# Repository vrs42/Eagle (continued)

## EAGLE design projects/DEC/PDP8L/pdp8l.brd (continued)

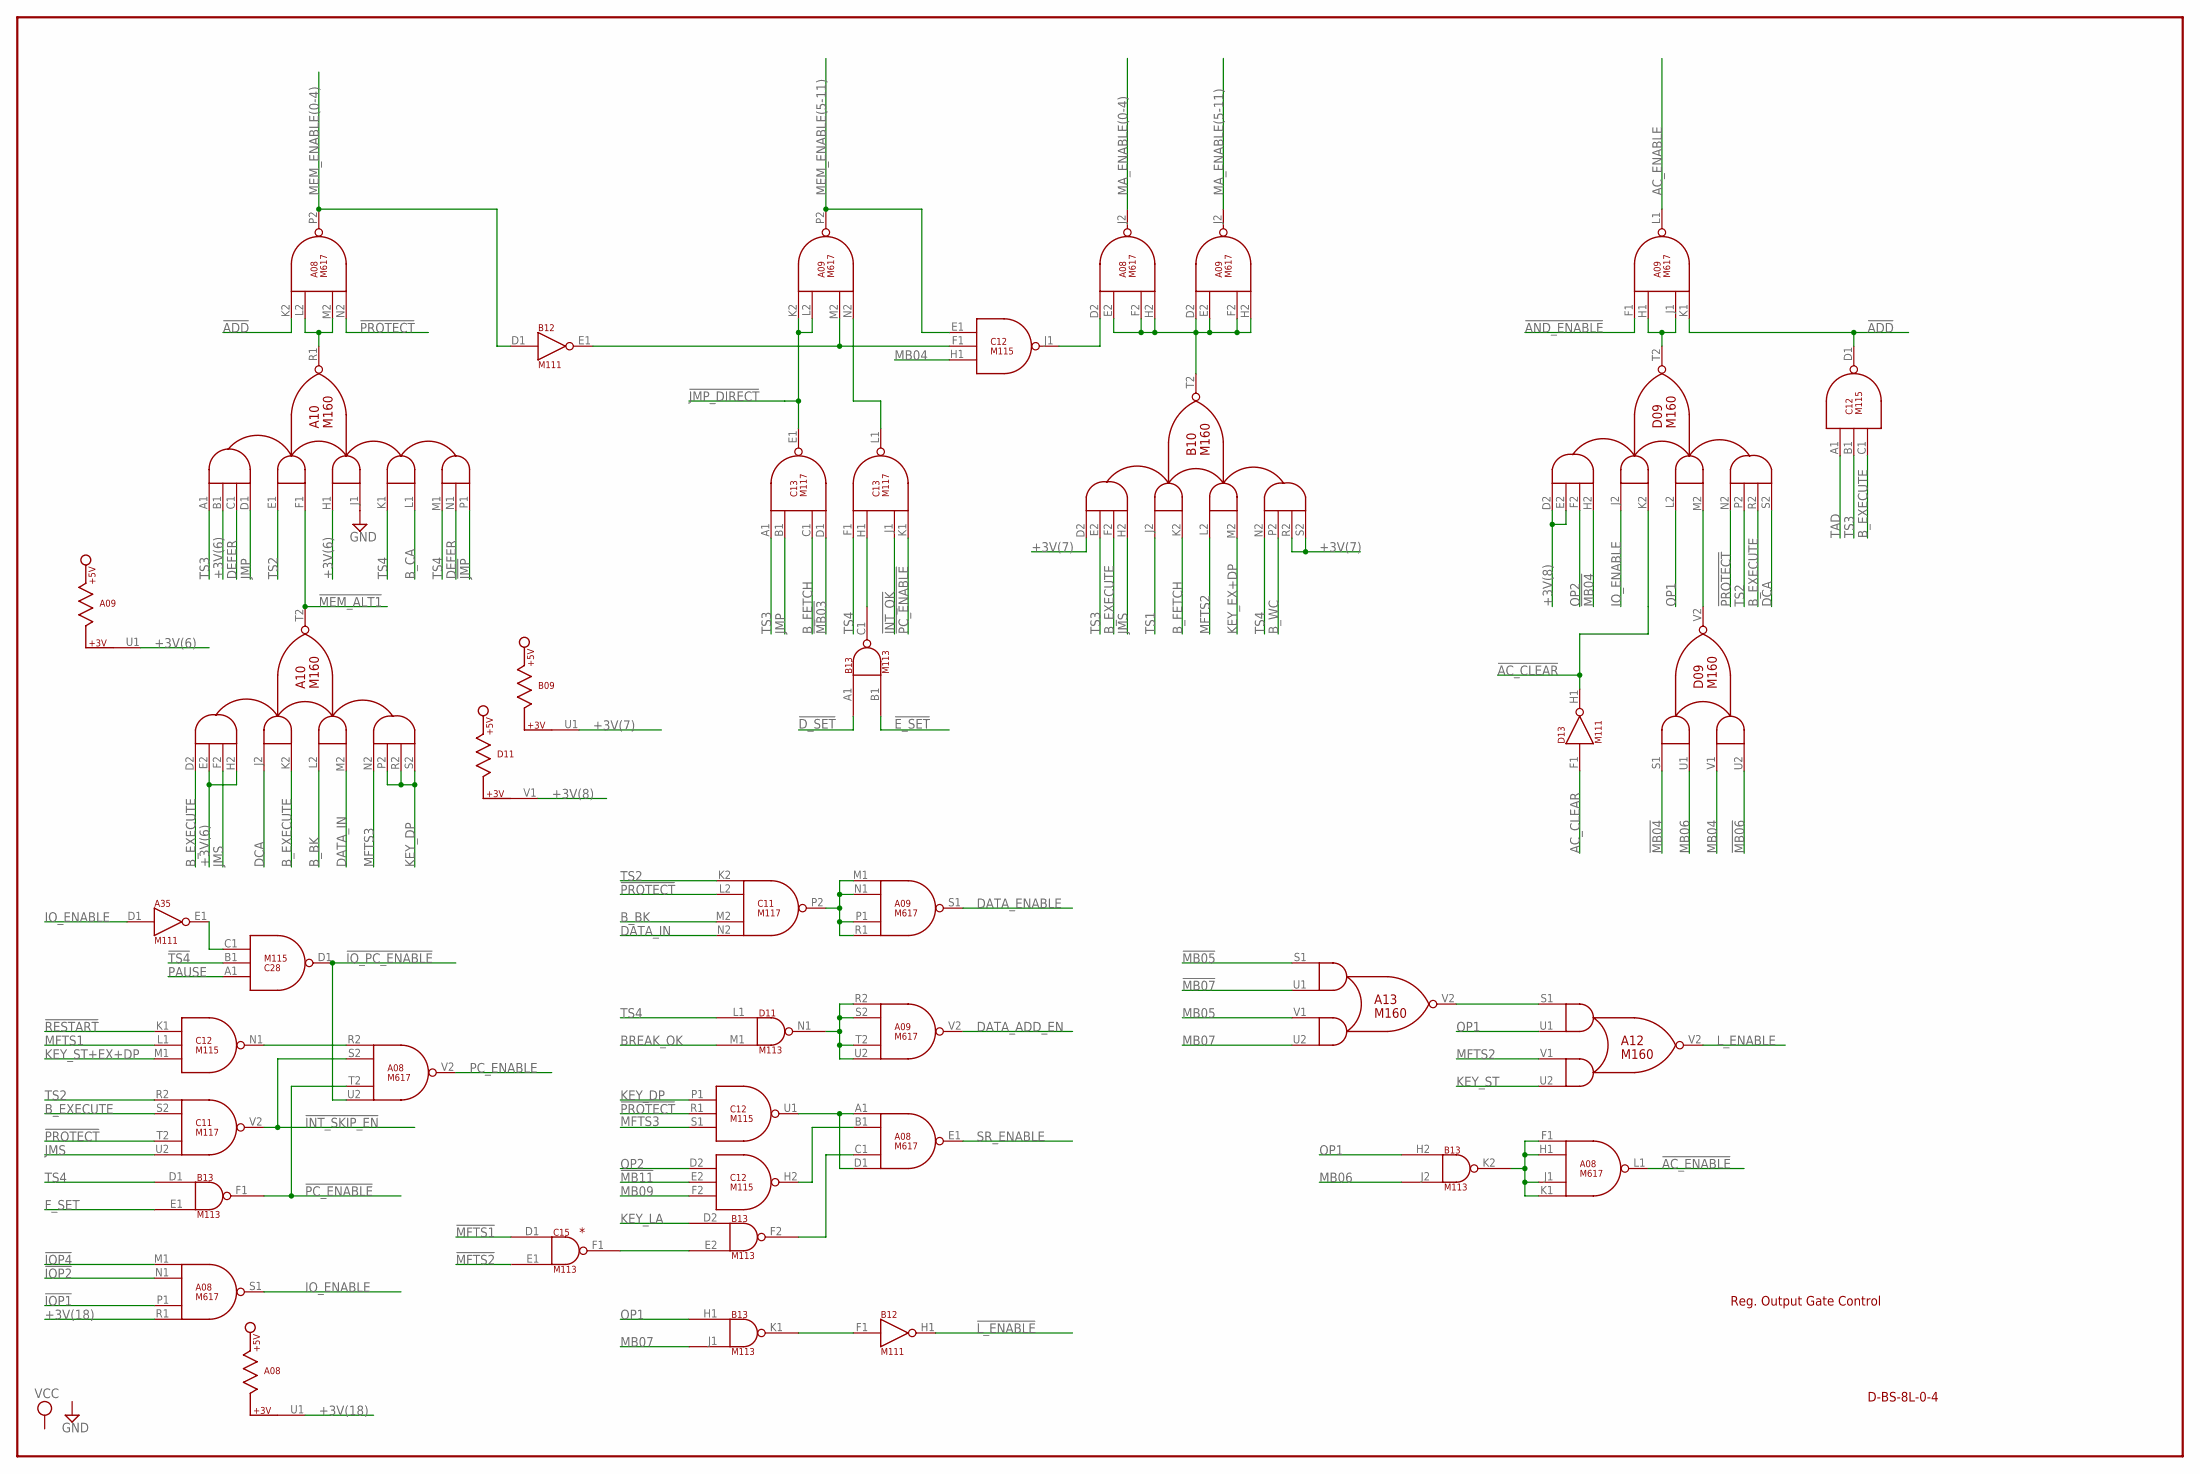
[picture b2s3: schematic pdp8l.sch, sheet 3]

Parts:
A08, A09: M617; H807
A10, A12, A13: M160; H807
A35: M111; H807
B09: M617; H807
B10: M160; H807
B12: M111; H807
B13: M113; H807
C11, C13: M117; H807
C12, C28: M115; H807
C15: M113; H807
D09: M160; H807
D11: M113; H807
D13: M111; H807

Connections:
!!AC_ENABLE: A08.F1 (IN1), A08.H1 (IN2), A08.J1 (IN3), A08.K1 (IN4), B13.K2 (OUT)
!!L_ENABLE: B12.F1 (IN), B13.K1 (OUT)
!AC_CLEAR: D09.K2 (IN2B), D13.H1 (OUT)
!AC_ENABLE: A08.L1 (OUT); also elsewhere on the board
!ADD: A08.K2 (IN1), A09.K1 (IN4), C12.D1 (OUT)
!AND_ENABLE: A09.F1 (IN1); also elsewhere on the board
!DATA_ADD_EN: A09.R2 (IN1), A09.S2 (IN2), A09.T2 (IN3), A09.U2 (IN4), D11.N1 (OUT)
!DATA_ENABLE: A09.M1 (IN1), A09.N1 (IN2), A09.P1 (IN3), A09.R1 (IN4), C11.P2 (OUT)
!D_SET: B13.A1 (IN1); also elsewhere on the board
!E_SET: B13.B1 (IN2); also elsewhere on the board
!INT_OK: C13.J1 (IN3); also elsewhere on the board
!INT_SKIP_EN: A08.S2 (IN2), C11.V2 (OUT); also elsewhere on the board
!IOP1: A08.P1 (IN3); also elsewhere on the board
!IOP2: A08.N1 (IN2); also elsewhere on the board
!IOP4: A08.M1 (IN1); also elsewhere on the board
!IO_ENABLE: A35.E1 (OUT), C28.C1 (IN3)
!IO_PC_ENABLE: A08.U2 (IN4), C28.D1 (OUT); also elsewhere on the board
!JMP: A10.P1 (IN5C); also elsewhere on the board
!JMP_DIRECT: A09.K2 (IN1), A09.L2 (IN2), C13.E1 (OUT); also elsewhere on the board
!L_ENABLE: B12.H1 (OUT); also elsewhere on the board
!MA_ENABLE(5-11): A08.E2 (IN2), A08.F2 (IN3), A08.H2 (IN4), A09.D2 (IN1), A09.E2 (IN2), A09.F2 (IN3), A09.H2 (IN4), B10.T2 (OUT)
!MB03: C13.D1 (IN4); also elsewhere on the board
!MB04: D09.H2 (IN1D), D09.S1 (IN1A); also elsewhere on the board
!MB05: A13.S1 (IN1A); also elsewhere on the board
!MB06: D09.U2 (IN2B); also elsewhere on the board
!MB07: A13.U1 (IN1B); also elsewhere on the board
!MB11: C12.E2 (IN2); also elsewhere on the board
!MEM_ALT1: A10.F1 (IN2B), A10.T2 (OUT); also elsewhere on the board
!MEM_ENABLE(0-4): A09.M2 (IN3), B12.E1 (OUT), C12.F1 (IN2)
!MFTS1: C15.D1 (IN1); also elsewhere on the board
!MFTS2: C15.E1 (IN2); also elsewhere on the board
!PC_ENABLE: A08.T2 (IN3), B13.F1 (OUT), C13.K1 (IN4); also elsewhere on the board
!PROTECT: A08.N2 (IN4), C11.L2 (IN2), C11.T2 (IN3), C12.R1 (IN2), D09.N2 (IN4A); also elsewhere on the board
!RESTART: C12.K1 (IN1); also elsewhere on the board
!TS4: C28.B1 (IN2); also elsewhere on the board
+3V(6): A09.U1, A10.B1 (IN1B), A10.E2 (IN1B), A10.H1 (IN3A), A10.H2 (IN1D)
+3V(7): B09.U1, B10.D2 (IN1A), B10.R2 (IN4C), B10.S2 (IN4D)
+3V(8): D09.D2 (IN1A), D09.E2 (IN1B), D11.V1; also elsewhere on the board
+3V(18): A08.R1 (IN4), A08.U1
A10R1: A08.L2 (IN2), A08.M2 (IN3), A10.R1 (OUT)
A13V2: A12.S1 (IN1A), A13.V2 (OUT)
AC_CLEAR: D13.F1 (IN); also elsewhere on the board
AC_ENABLE: A09.L1 (OUT); also elsewhere on the board
B13C1: B13.C1 (OUT), C13.H1 (IN2)
B13F2: A08.C1 (IN3), B13.F2 (OUT)
BREAK_OK: D11.M1 (IN2); also elsewhere on the board
B_BK: A10.L2 (IN3A), C11.M2 (IN3); also elsewhere on the board
B_CA: A10.L1 (IN4B); also elsewhere on the board
B_EXECUTE: A10.D2 (IN1A), A10.K2 (IN2B), B10.F2 (IN1C), C11.S2 (IN2), C12.C1 (IN3), D09.R2 (IN4C); also elsewhere on the board
B_FETCH: B10.K2 (IN2B), C13.C1 (IN3); also elsewhere on the board
B_WC: B10.P2 (IN4B); also elsewhere on the board
C12H2: A08.B1 (IN2), C12.H2 (OUT)
C12J1: A08.D2 (IN1), C12.J1 (OUT)
C12N1: A08.R2 (IN1), C12.N1 (OUT)
C12U1: A08.A1 (IN1), A08.D1 (IN4), C12.U1 (OUT)
C13L1: A09.N2 (IN4), C13.L1 (OUT)
C15F1: B13.E2 (IN2), C15.F1 (OUT)
D09T2: A09.H1 (IN2), A09.J1 (IN3), D09.T2 (OUT)
D09V2: D09.M2 (IN3B), D09.V2 (OUT)
DATA_ADD_EN: A09.V2 (OUT); also elsewhere on the board
DATA_ENABLE: A09.S1 (OUT); also elsewhere on the board
DATA_IN: A10.M2 (IN3B), C11.N2 (IN4); also elsewhere on the board
DCA: A10.J2 (IN2A), D09.S2 (IN4D); also elsewhere on the board
DEFER: A10.C1 (IN1C), A10.N1 (IN5B); also elsewhere on the board
F_SET: B13.E1 (IN2); also elsewhere on the board
GND: A08.C2 (GND), A08.T1 (GND), A09.C2 (GND), A09.T1 (GND), A10.C2 (GND), A10.J1 (IN3B), A10.T1 (GND), A12.C2 (GND), A12.T1 (GND), A13.C2 (GND), A13.T1 (GND), A35.C2 (GND), A35.T1 (GND), B09.C2 (GND), B09.T1 (GND), B10.C2 (GND), B10.T1 (GND), B12.C2 (GND), B12.T1 (GND), B13.C2 (GND), B13.T1 (GND), C11.C2 (GND), C11.T1 (GND), C12.C2 (GND), C12.T1 (GND), C13.C2 (GND), C13.T1 (GND), C15.C2 (GND), C15.T1 (GND), C28.C2 (GND), C28.T1 (GND), D09.C2 (GND), D09.T1 (GND), D11.C2 (GND), D11.T1 (GND), D13.C2 (GND), D13.T1 (GND); also elsewhere on the board
IO_ENABLE: A08.S1 (OUT), A35.D1 (IN), D09.J2 (IN2A); also elsewhere on the board
JMP: A10.D1 (IN1D), C13.B1 (IN2); also elsewhere on the board
JMS: A10.F2 (IN1C), B10.H2 (IN1D), C11.U2 (IN4); also elsewhere on the board
KEY_DP: A10.P2 (IN4B), A10.R2 (IN4C), A10.S2 (IN4D), C12.P1 (IN1); also elsewhere on the board
KEY_EX+DP: B10.M2 (IN3B); also elsewhere on the board
KEY_LA: B13.D2 (IN1); also elsewhere on the board
KEY_ST: A12.U2 (IN2B); also elsewhere on the board
KEY_ST+EX+DP: C12.M1 (IN3); also elsewhere on the board
L_ENABLE: A12.V2 (OUT); also elsewhere on the board
MA_ENABLE(0-4): A08.J2 (OUT); also elsewhere on the board
MA_ENABLE(5-11): A09.J2 (OUT); also elsewhere on the board
MB04: C12.H1 (IN3), D09.V1 (IN2A); also elsewhere on the board
MB05: A13.V1 (IN2A); also elsewhere on the board
MB06: B13.J2 (IN2), D09.U1 (IN1B); also elsewhere on the board
MB07: A13.U2 (IN2B), B13.J1 (IN2); also elsewhere on the board
MB09: C12.F2 (IN3); also elsewhere on the board
MEM_ENABLE(0-4): A08.P2 (OUT), B12.D1 (IN); also elsewhere on the board
MEM_ENABLE(5-11): A09.P2 (OUT), C12.E1 (IN1); also elsewhere on the board
MFTS1: C12.L1 (IN2); also elsewhere on the board
MFTS2: A12.V1 (IN2A), B10.L2 (IN3A); also elsewhere on the board
MFTS3: A10.N2 (IN4A), C12.S1 (IN3); also elsewhere on the board
OP1: A12.U1 (IN1B), B13.H1 (IN1), B13.H2 (IN1), D09.L2 (IN3A); also elsewhere on the board
OP2: C12.D2 (IN1), D09.F2 (IN1C); also elsewhere on the board
PAUSE: C28.A1 (IN1); also elsewhere on the board
PC_ENABLE: A08.V2 (OUT); also elsewhere on the board
SR_ENABLE: A08.E1 (OUT); also elsewhere on the board
TAD: C12.A1 (IN1); also elsewhere on the board
TS1: B10.J2 (IN2A); also elsewhere on the board
TS2: A10.E1 (IN2A), C11.K2 (IN1), C11.R2 (IN1), D09.P2 (IN4B); also elsewhere on the board
TS3: A10.A1 (IN1A), B10.E2 (IN1B), C12.B1 (IN2), C13.A1 (IN1); also elsewhere on the board
TS4: A10.K1 (IN4A), A10.M1 (IN5A), B10.N2 (IN4A), B13.D1 (IN1), C13.F1 (IN1), D11.L1 (IN1); also elsewhere on the board
VCC: A08.A2 (VCC), A09.A2 (VCC), A10.A2 (VCC), A12.A2 (VCC), A13.A2 (VCC), A35.A2 (VCC), B09.A2 (VCC), B10.A2 (VCC), B12.A2 (VCC), B13.A2 (VCC), C11.A2 (VCC), C12.A2 (VCC), C13.A2 (VCC), C15.A2 (VCC), C28.A2 (VCC), D09.A2 (VCC), D11.A2 (VCC), D13.A2 (VCC); also elsewhere on the board

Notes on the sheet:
D-BS-8L-0-4
Reg. Output Gate Control

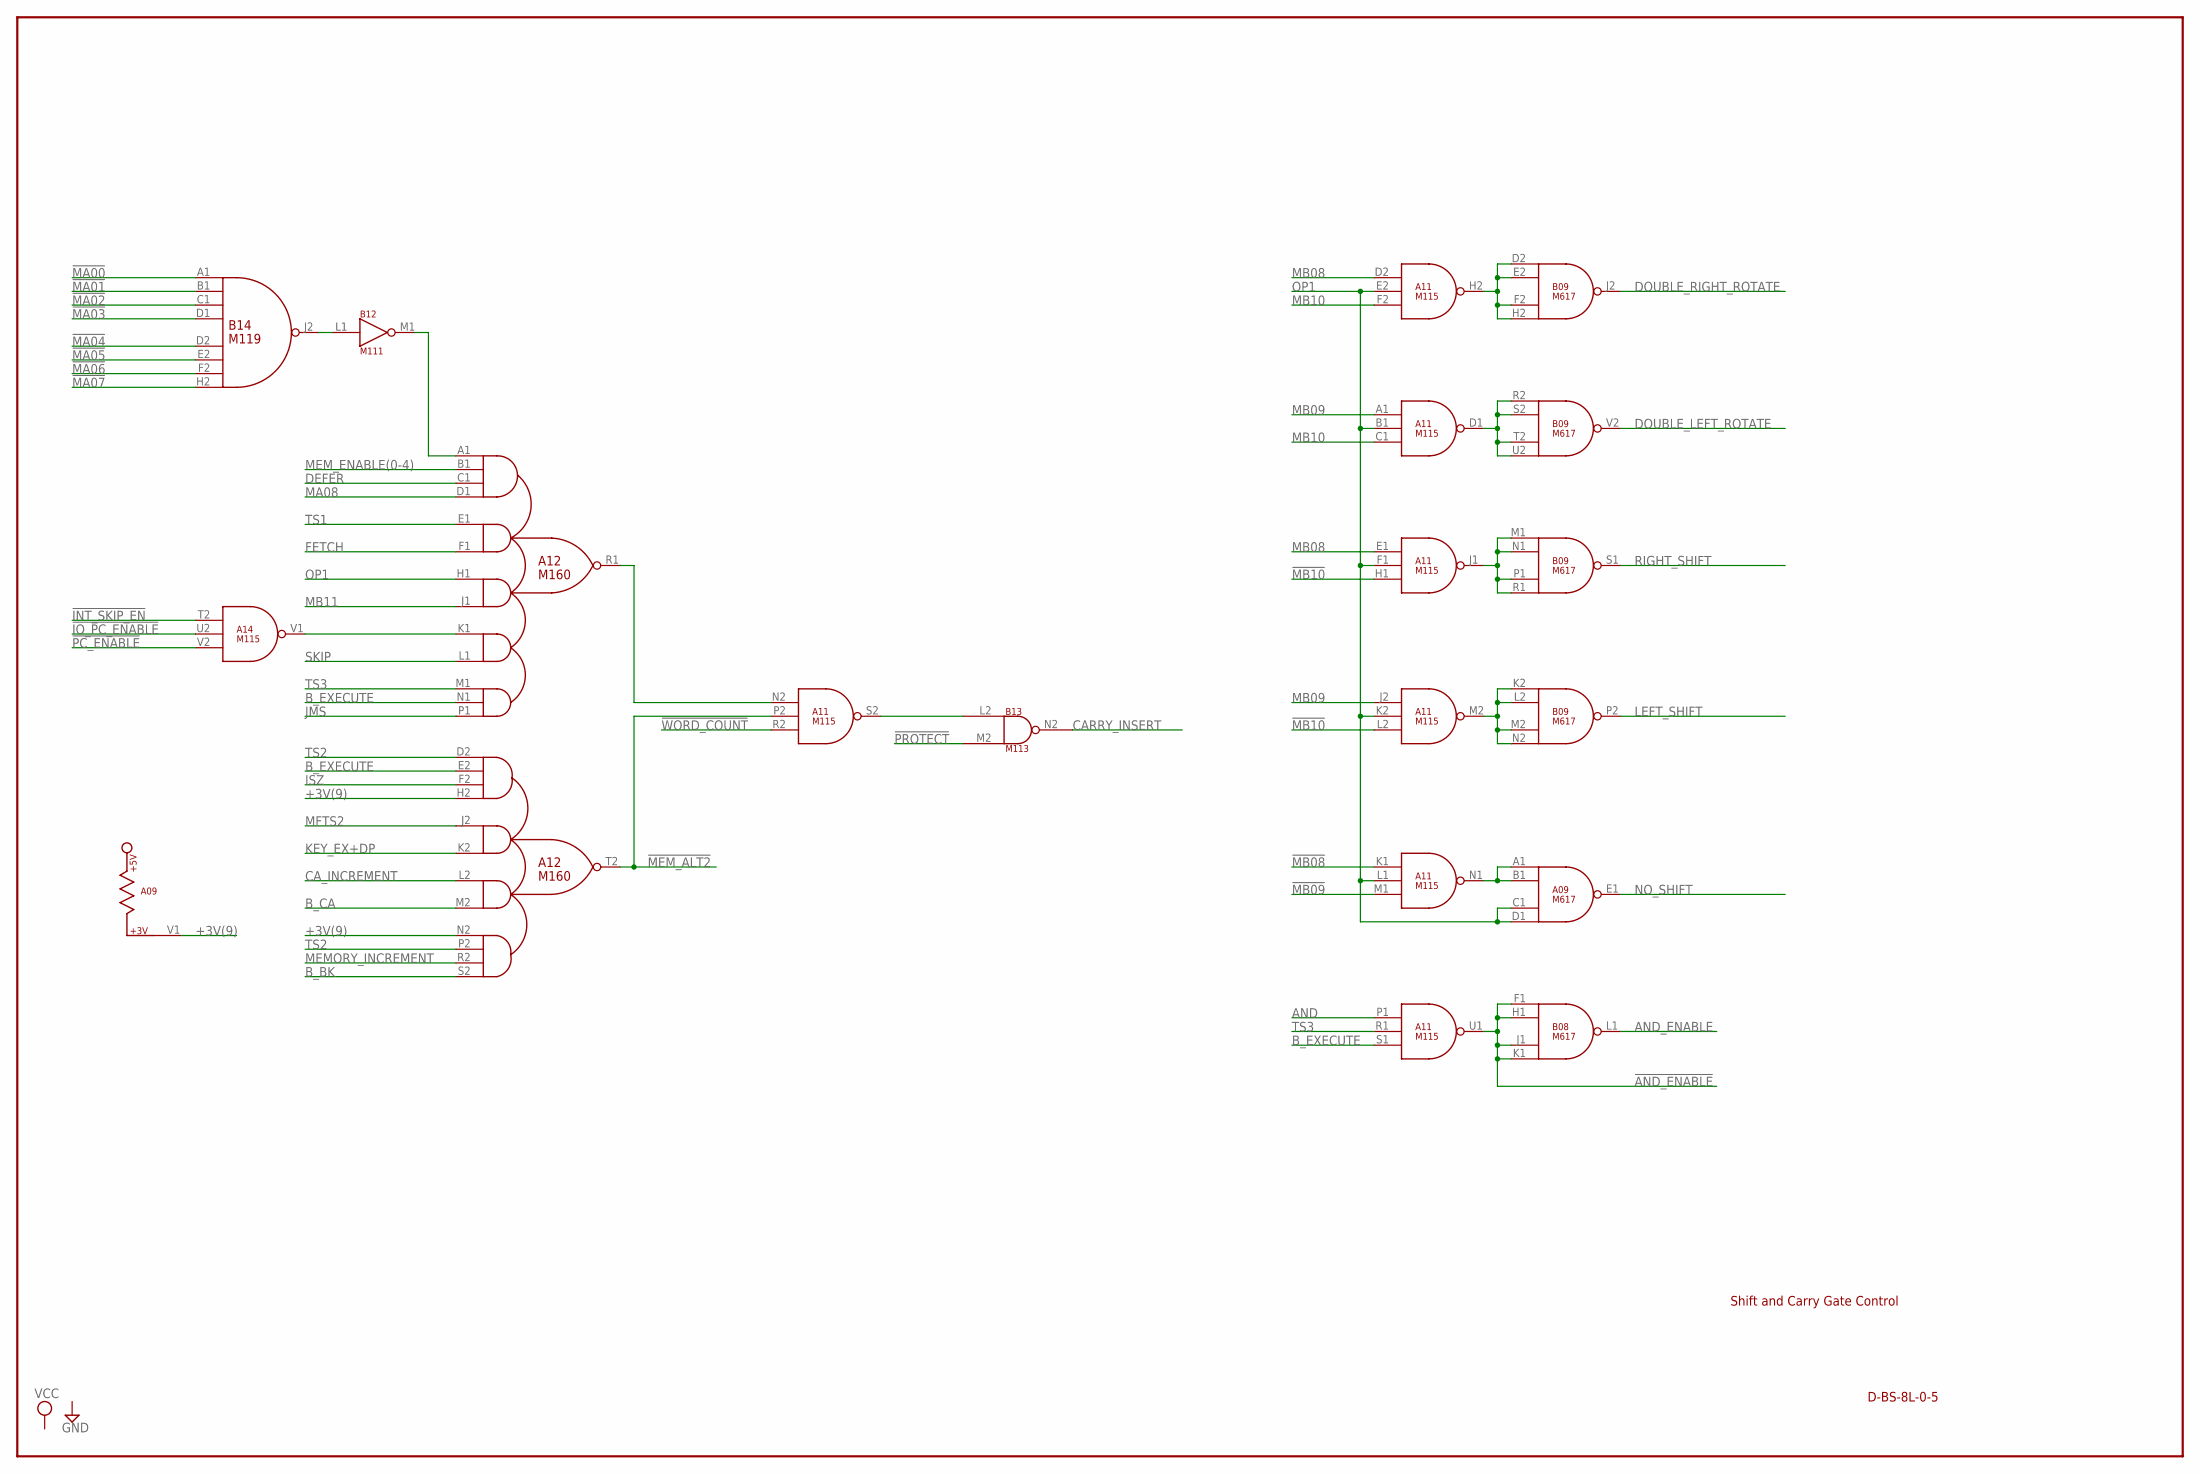
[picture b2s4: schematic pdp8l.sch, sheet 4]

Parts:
A09: M617; H807
A11, A14: M115; H807
A12: M160; H807
B08, B09: M617; H807
B12: M111; H807
B13: M113; H807
B14: M119; H807

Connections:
!AND_ENABLE: A11.U1 (OUT), B08.F1 (IN1), B08.H1 (IN2), B08.J1 (IN3), B08.K1 (IN4); also elsewhere on the board
!DOUBLE_LEFT_ROTATE: A11.D1 (OUT), B09.R2 (IN1), B09.S2 (IN2), B09.T2 (IN3), B09.U2 (IN4)
!DOUBLE_RIGHT_ROTATE: A11.H2 (OUT), B09.D2 (IN1), B09.E2 (IN2), B09.F2 (IN3), B09.H2 (IN4)
!INT_SKIP_EN: A14.T2 (IN1); also elsewhere on the board
!IO_PC_ENABLE: A14.U2 (IN2); also elsewhere on the board
!LEFT_SHIFT: A11.M2 (OUT), B09.K2 (IN1), B09.L2 (IN2), B09.M2 (IN3), B09.N2 (IN4)
!MA00: B14.A1 (IN1); also elsewhere on the board
!MA01: B14.B1 (IN2); also elsewhere on the board
!MA02: B14.C1 (IN3); also elsewhere on the board
!MA03: B14.D1 (IN4); also elsewhere on the board
!MA04: B14.D2 (IN5); also elsewhere on the board
!MA05: B14.E2 (IN6); also elsewhere on the board
!MA06: B14.F2 (IN7); also elsewhere on the board
!MA07: B14.H2 (IN8); also elsewhere on the board
!MB08: A11.K1 (IN1); also elsewhere on the board
!MB09: A11.M1 (IN3); also elsewhere on the board
!MB10: A11.H1 (IN3), A11.L2 (IN3); also elsewhere on the board
!MEM_ALT2: A11.P2 (IN2), A12.T2 (OUT); also elsewhere on the board
!PC_ENABLE: A14.V2 (IN3); also elsewhere on the board
!PROTECT: B13.M2 (IN2); also elsewhere on the board
!RIGHT_SHIFT: A11.J1 (OUT), B09.M1 (IN1), B09.N1 (IN2), B09.P1 (IN3), B09.R1 (IN4)
!WORD_COUNT: A11.R2 (IN3); also elsewhere on the board
+3V(9): A09.V1, A12.H2 (IN1D), A12.N2 (IN4A)
A11N1: A09.A1 (IN1), A09.B1 (IN2), A11.N1 (OUT)
A11S2: A11.S2 (OUT), B13.L2 (IN1)
A12R1: A11.N2 (IN1), A12.R1 (OUT)
A14V1: A12.K1 (IN4A), A14.V1 (OUT)
AND: A11.P1 (IN1); also elsewhere on the board
AND_ENABLE: B08.L1 (OUT); also elsewhere on the board
B12M1: A12.A1 (IN1A), B12.M1 (OUT)
B14J2: B12.L1 (IN), B14.J2 (OUT)
B_BK: A12.S2 (IN4D); also elsewhere on the board
B_CA: A12.M2 (IN3B); also elsewhere on the board
B_EXECUTE: A11.S1 (IN3), A12.E2 (IN1B), A12.N1 (IN5B); also elsewhere on the board
CARRY_INSERT: B13.N2 (OUT); also elsewhere on the board
CA_INCREMENT: A12.L2 (IN3A); also elsewhere on the board
DEFER: A12.C1 (IN1C); also elsewhere on the board
DOUBLE_LEFT_ROTATE: B09.V2 (OUT); also elsewhere on the board
DOUBLE_RIGHT_ROTATE: B09.J2 (OUT); also elsewhere on the board
FETCH: A12.F1 (IN2B); also elsewhere on the board
GND: A09.C2 (GND), A09.T1 (GND), A11.C2 (GND), A11.T1 (GND), A12.C2 (GND), A12.T1 (GND), A14.C2 (GND), A14.T1 (GND), B08.C2 (GND), B08.T1 (GND), B09.C2 (GND), B09.T1 (GND), B12.C2 (GND), B12.T1 (GND), B13.C2 (GND), B13.T1 (GND), B14.C2 (GND), B14.T1 (GND); also elsewhere on the board
ISZ: A12.F2 (IN1C); also elsewhere on the board
JMS: A12.P1 (IN5C); also elsewhere on the board
KEY_EX+DP: A12.K2 (IN2B); also elsewhere on the board
LEFT_SHIFT: B09.P2 (OUT); also elsewhere on the board
MA08: A12.D1 (IN1D); also elsewhere on the board
MB08: A11.D2 (IN1), A11.E1 (IN1); also elsewhere on the board
MB09: A11.A1 (IN1), A11.J2 (IN1); also elsewhere on the board
MB10: A11.C1 (IN3), A11.F2 (IN3); also elsewhere on the board
MB11: A12.J1 (IN3B); also elsewhere on the board
MEMORY_INCREMENT: A12.R2 (IN4C); also elsewhere on the board
MEM_ENABLE(0-4): A12.B1 (IN1B); also elsewhere on the board
MFTS2: A12.J2 (IN2A); also elsewhere on the board
NO_SHIFT: A09.E1 (OUT); also elsewhere on the board
OP1: A09.C1 (IN3), A09.D1 (IN4), A11.B1 (IN2), A11.E2 (IN2), A11.F1 (IN2), A11.K2 (IN2), A11.L1 (IN2), A12.H1 (IN3A); also elsewhere on the board
RIGHT_SHIFT: B09.S1 (OUT); also elsewhere on the board
SKIP: A12.L1 (IN4B); also elsewhere on the board
TS1: A12.E1 (IN2A); also elsewhere on the board
TS2: A12.D2 (IN1A), A12.P2 (IN4B); also elsewhere on the board
TS3: A11.R1 (IN2), A12.M1 (IN5A); also elsewhere on the board
VCC: A09.A2 (VCC), A11.A2 (VCC), A12.A2 (VCC), A14.A2 (VCC), B08.A2 (VCC), B09.A2 (VCC), B12.A2 (VCC), B13.A2 (VCC), B14.A2 (VCC); also elsewhere on the board

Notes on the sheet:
D-BS-8L-0-5
Shift and Carry Gate Control

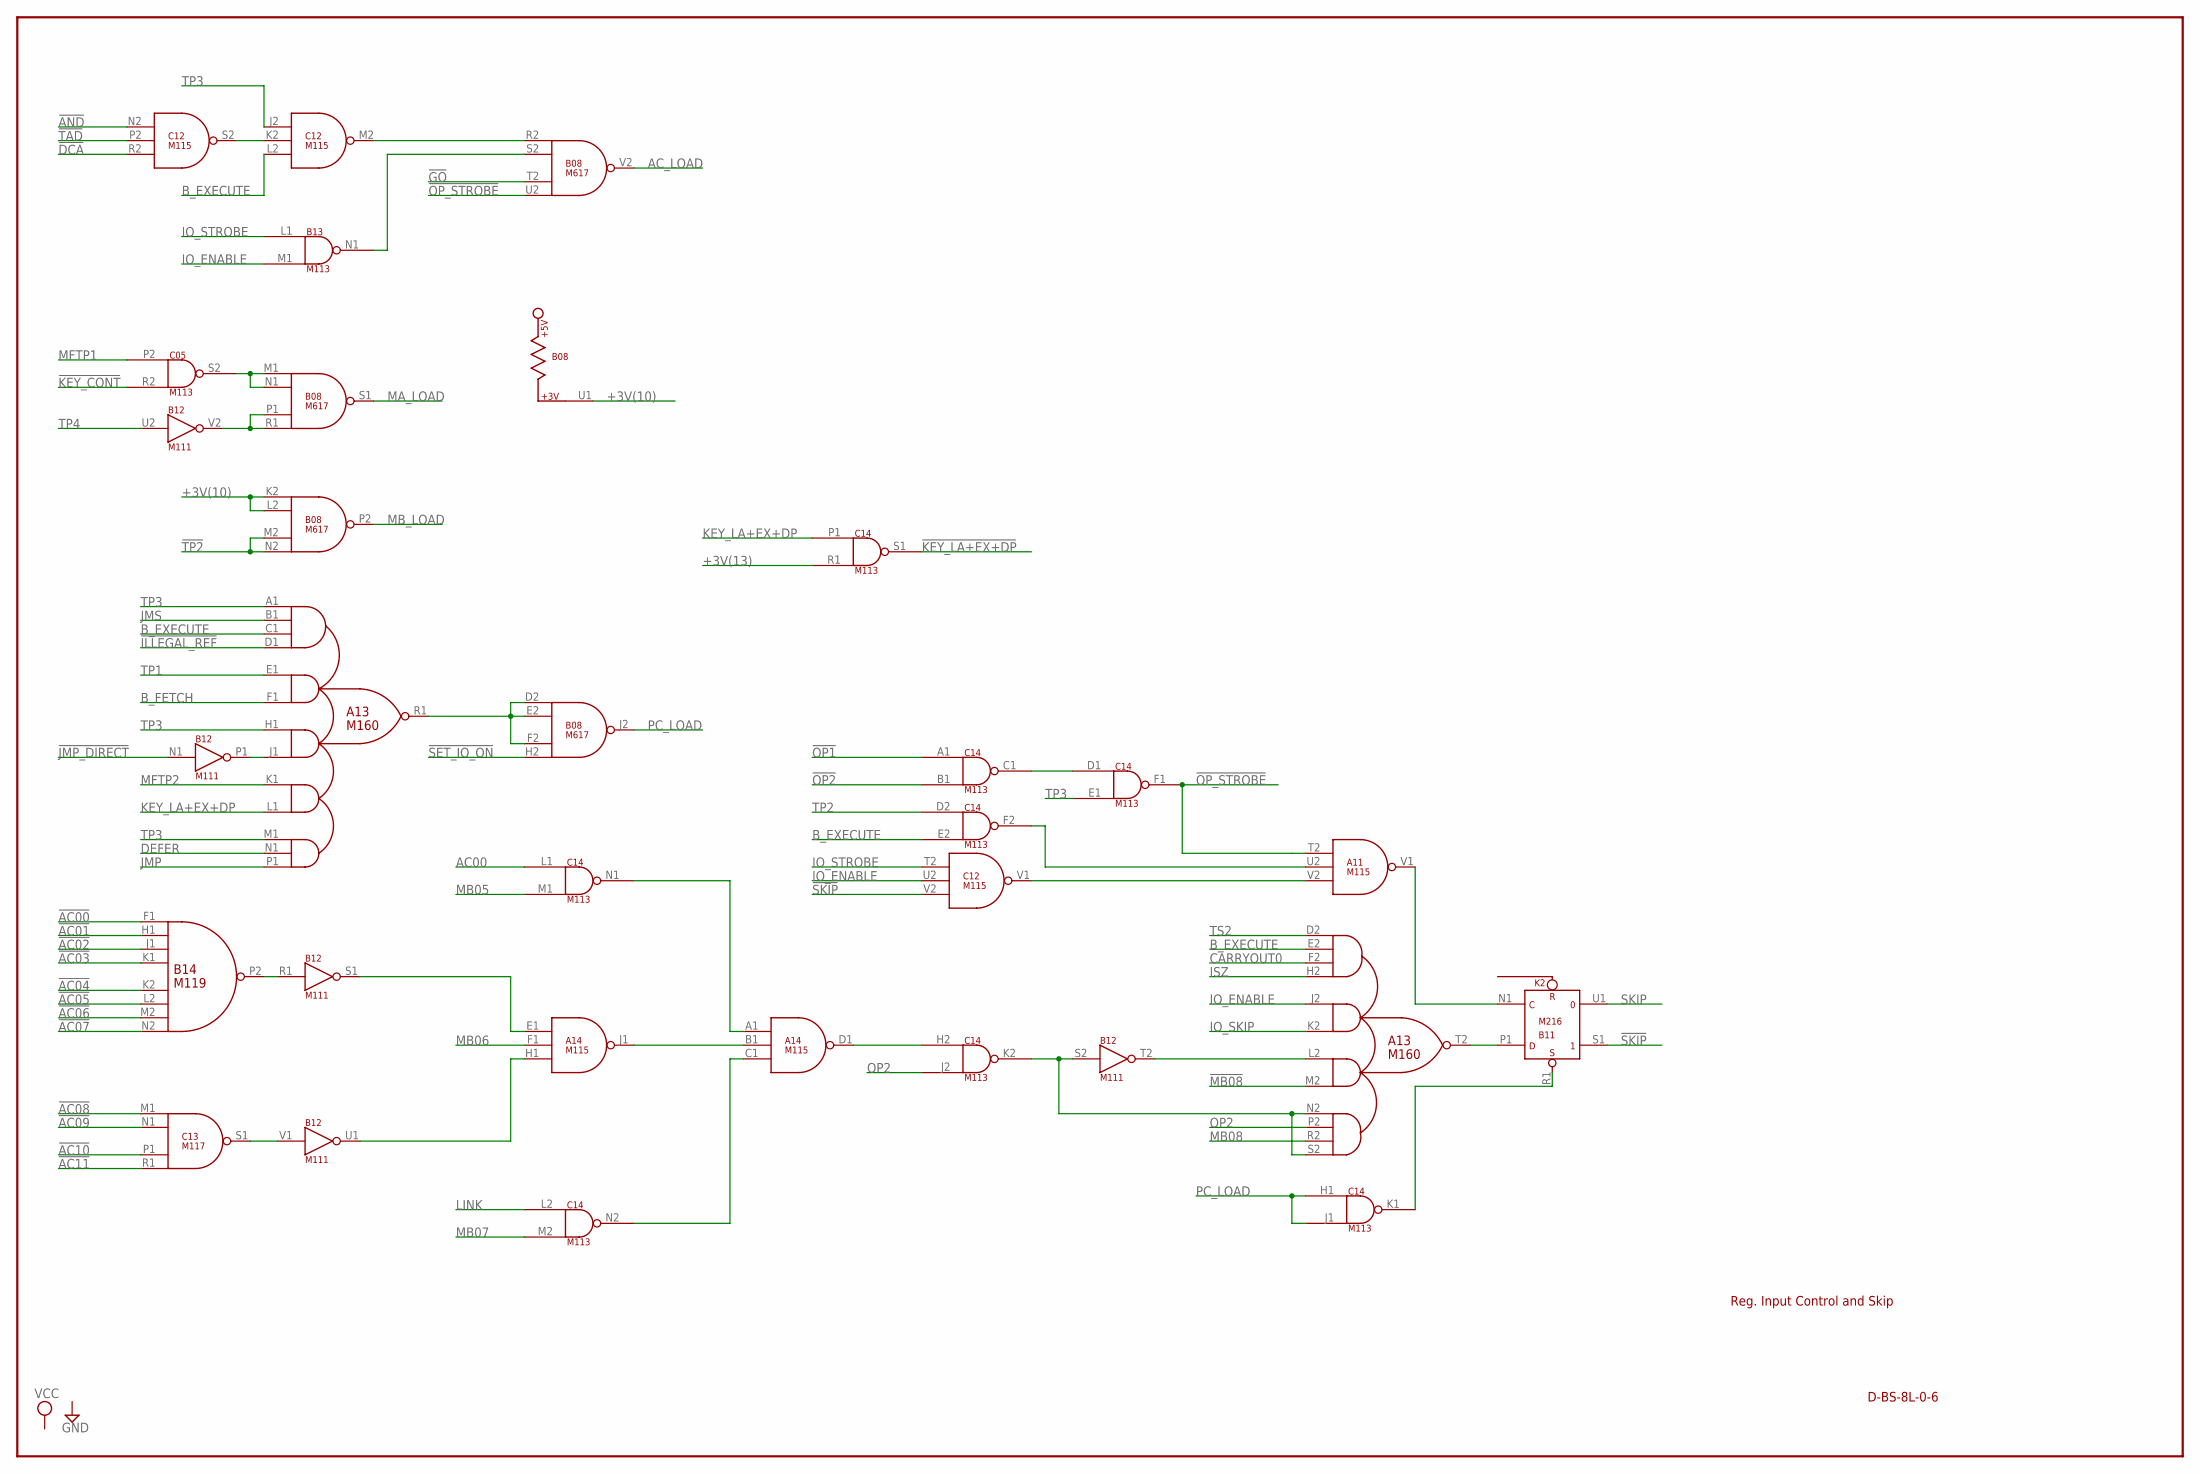
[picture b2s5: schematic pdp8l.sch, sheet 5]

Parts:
A11, A14: M115; H807
A13: M160; H807
B08: M617; H807
B11: M216; H807
B12: M111; H807
B13: M113; H807
B14: M119; H807
C05, C14: M113; H807
C12: M115; H807
C13: M117; H807

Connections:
!AC00: B14.F1 (IN1); also elsewhere on the board
!AC01: B14.H1 (IN2); also elsewhere on the board
!AC02: B14.J1 (IN3); also elsewhere on the board
!AC03: B14.K1 (IN4); also elsewhere on the board
!AC04: B14.K2 (IN5); also elsewhere on the board
!AC05: B14.L2 (IN6); also elsewhere on the board
!AC06: B14.M2 (IN7); also elsewhere on the board
!AC07: B14.N2 (IN8); also elsewhere on the board
!AC08: C13.M1 (IN1); also elsewhere on the board
!AC09: C13.N1 (IN2); also elsewhere on the board
!AC10: C13.P1 (IN3); also elsewhere on the board
!AC11: C13.R1 (IN4); also elsewhere on the board
!AND: C12.N2 (IN1); also elsewhere on the board
!DCA: C12.R2 (IN3); also elsewhere on the board
!GO: B08.T2 (IN3); also elsewhere on the board
!ILLEGAL_REF: A13.D1 (IN1D); also elsewhere on the board
!JMP_DIRECT: B12.N1 (IN); also elsewhere on the board
!KEY_CONT: C05.R2 (IN2); also elsewhere on the board
!KEY_LA+EX+DP: C14.S1 (OUT); also elsewhere on the board
!MB08: A13.M2 (IN3B); also elsewhere on the board
!OP1: C14.A1 (IN1); also elsewhere on the board
!OP2: C14.B1 (IN2); also elsewhere on the board
!OP_STROBE: A11.T2 (IN1), B08.U2 (IN4), C14.F1 (OUT)
!PC_LOAD: B11.R1 (S), C14.K1 (OUT)
!SET_IO_ON: B08.H2 (IN4); also elsewhere on the board
!SKIP: B11.S1 (1), C12.V2 (IN3)
!TAD: C12.P2 (IN2); also elsewhere on the board
!TP2: B08.M2 (IN3), B08.N2 (IN4); also elsewhere on the board
!TP4: B08.P1 (IN3), B08.R1 (IN4), B12.V2 (OUT)
+3V(10): B08.K2 (IN1), B08.L2 (IN2), B08.U1
+3V(13): C14.R1 (IN2); also elsewhere on the board
A11V1: A11.V1 (OUT), B11.N1 (C)
A13R1: A13.R1 (OUT), B08.D2 (IN1), B08.E2 (IN2), B08.F2 (IN3)
A13T2: A13.T2 (OUT), B11.P1 (D)
A14D1: A14.D1 (OUT), C14.H2 (IN1)
A14J1: A14.B1 (IN2), A14.J1 (OUT)
AC00: C14.L1 (IN1); also elsewhere on the board
AC_LOAD: B08.V2 (OUT); also elsewhere on the board
B12S1: A14.E1 (IN1), B12.S1 (OUT)
B12T2: A13.L2 (IN3A), B12.T2 (OUT)
B12U1: A14.H1 (IN3), B12.U1 (OUT)
B13N1: B08.S2 (IN2), B13.N1 (OUT)
B14P2: B12.R1 (IN), B14.P2 (OUT)
B_EXECUTE: A13.C1 (IN1C), A13.E2 (IN1B), C12.L2 (IN3), C14.E2 (IN2); also elsewhere on the board
B_FETCH: A13.F1 (IN2B); also elsewhere on the board
C05S2: B08.M1 (IN1), B08.N1 (IN2), C05.S2 (OUT)
C12M2: B08.R2 (IN1), C12.M2 (OUT)
C12S2: C12.K2 (IN2), C12.S2 (OUT)
C12V1: A11.V2 (IN3), C12.V1 (OUT)
C13S1: B12.V1 (IN), C13.S1 (OUT)
C14C1: C14.C1 (OUT), C14.D1 (IN1)
C14F2: A11.U2 (IN2), C14.F2 (OUT)
C14K2: A13.N2 (IN4A), A13.S2 (IN4D), B12.S2 (IN), C14.K2 (OUT)
C14N1: A14.A1 (IN1), C14.N1 (OUT)
C14N2: A14.C1 (IN3), C14.N2 (OUT)
CARRYOUT0: A13.F2 (IN1C); also elsewhere on the board
DEFER: A13.N1 (IN5B); also elsewhere on the board
GND: A11.C2 (GND), A11.T1 (GND), A13.C2 (GND), A13.T1 (GND), A14.C2 (GND), A14.T1 (GND), B08.C2 (GND), B08.T1 (GND), B11.C2 (GND), B11.T1 (GND), B12.C2 (GND), B12.T1 (GND), B13.C2 (GND), B13.T1 (GND), B14.C2 (GND), B14.T1 (GND), C05.C2 (GND), C05.T1 (GND), C12.C2 (GND), C12.T1 (GND), C13.C2 (GND), C13.T1 (GND), C14.C2 (GND), C14.T1 (GND); also elsewhere on the board
IO_ENABLE: A13.J2 (IN2A), B13.M1 (IN2), C12.U2 (IN2); also elsewhere on the board
IO_SKIP: A13.K2 (IN2B); also elsewhere on the board
IO_STROBE: B13.L1 (IN1), C12.T2 (IN1); also elsewhere on the board
ISZ: A13.H2 (IN1D); also elsewhere on the board
JMP: A13.P1 (IN5C); also elsewhere on the board
JMP_DIRECT: A13.J1 (IN3B), B12.P1 (OUT)
JMS: A13.B1 (IN1B); also elsewhere on the board
KEY_LA+EX+DP: A13.L1 (IN4B), C14.P1 (IN1); also elsewhere on the board
LINK: C14.L2 (IN1); also elsewhere on the board
MA_LOAD: B08.S1 (OUT); also elsewhere on the board
MB05: C14.M1 (IN2); also elsewhere on the board
MB06: A14.F1 (IN2); also elsewhere on the board
MB07: C14.M2 (IN2); also elsewhere on the board
MB08: A13.R2 (IN4C); also elsewhere on the board
MB_LOAD: B08.P2 (OUT); also elsewhere on the board
MFTP1: C05.P2 (IN1); also elsewhere on the board
MFTP2: A13.K1 (IN4A); also elsewhere on the board
OP2: A13.P2 (IN4B), C14.J2 (IN2); also elsewhere on the board
PC_LOAD: B08.J2 (OUT), C14.H1 (IN1), C14.J1 (IN2); also elsewhere on the board
SKIP: B11.U1 (0); also elsewhere on the board
TP1: A13.E1 (IN2A); also elsewhere on the board
TP2: C14.D2 (IN1); also elsewhere on the board
TP3: A13.A1 (IN1A), A13.H1 (IN3A), A13.M1 (IN5A), C12.J2 (IN1), C14.E1 (IN2); also elsewhere on the board
TP4: B12.U2 (IN); also elsewhere on the board
TS2: A13.D2 (IN1A); also elsewhere on the board
VCC: A11.A2 (VCC), A13.A2 (VCC), A14.A2 (VCC), B08.A2 (VCC), B11.A2 (VCC), B12.A2 (VCC), B13.A2 (VCC), B14.A2 (VCC), C05.A2 (VCC), C12.A2 (VCC), C13.A2 (VCC), C14.A2 (VCC); also elsewhere on the board

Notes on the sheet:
D-BS-8L-0-6
Reg. Input Control and Skip
